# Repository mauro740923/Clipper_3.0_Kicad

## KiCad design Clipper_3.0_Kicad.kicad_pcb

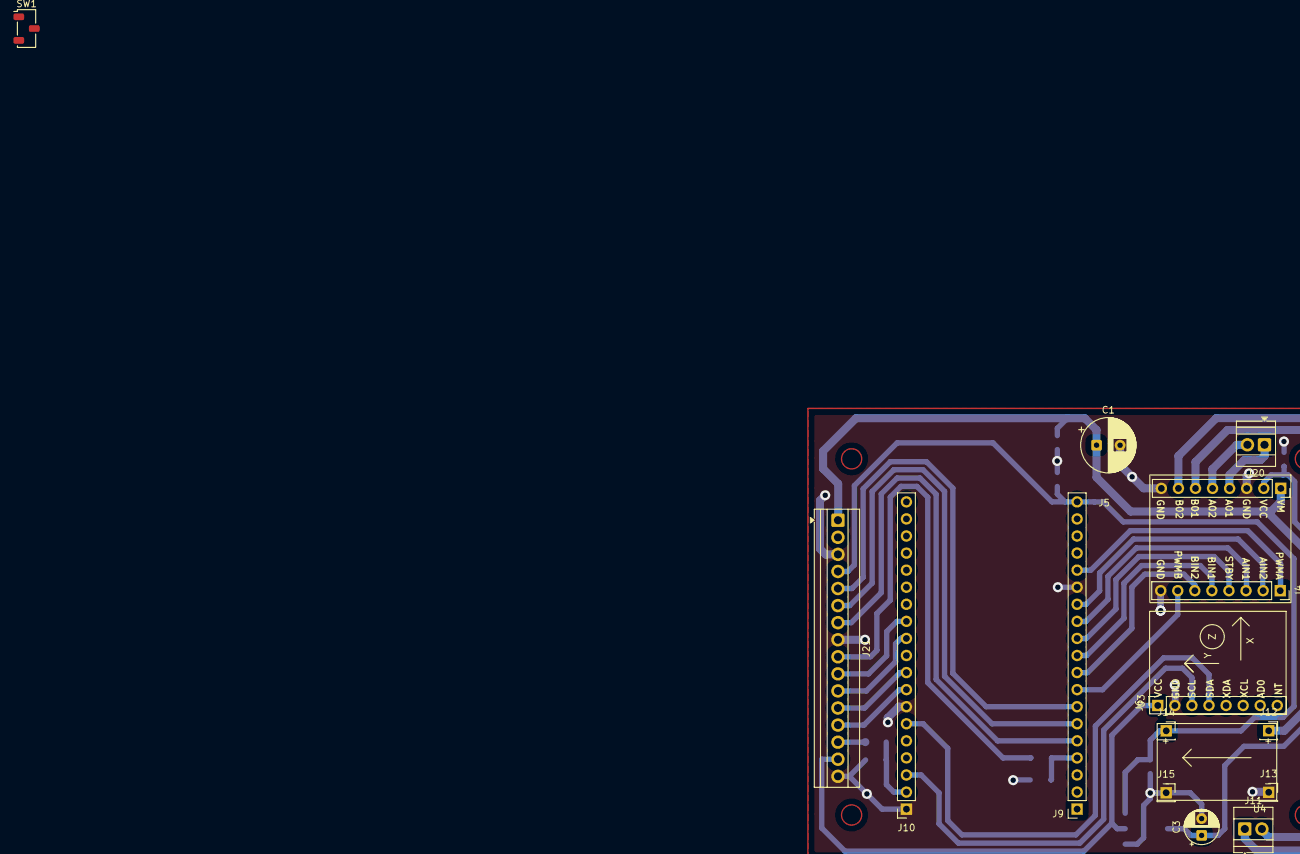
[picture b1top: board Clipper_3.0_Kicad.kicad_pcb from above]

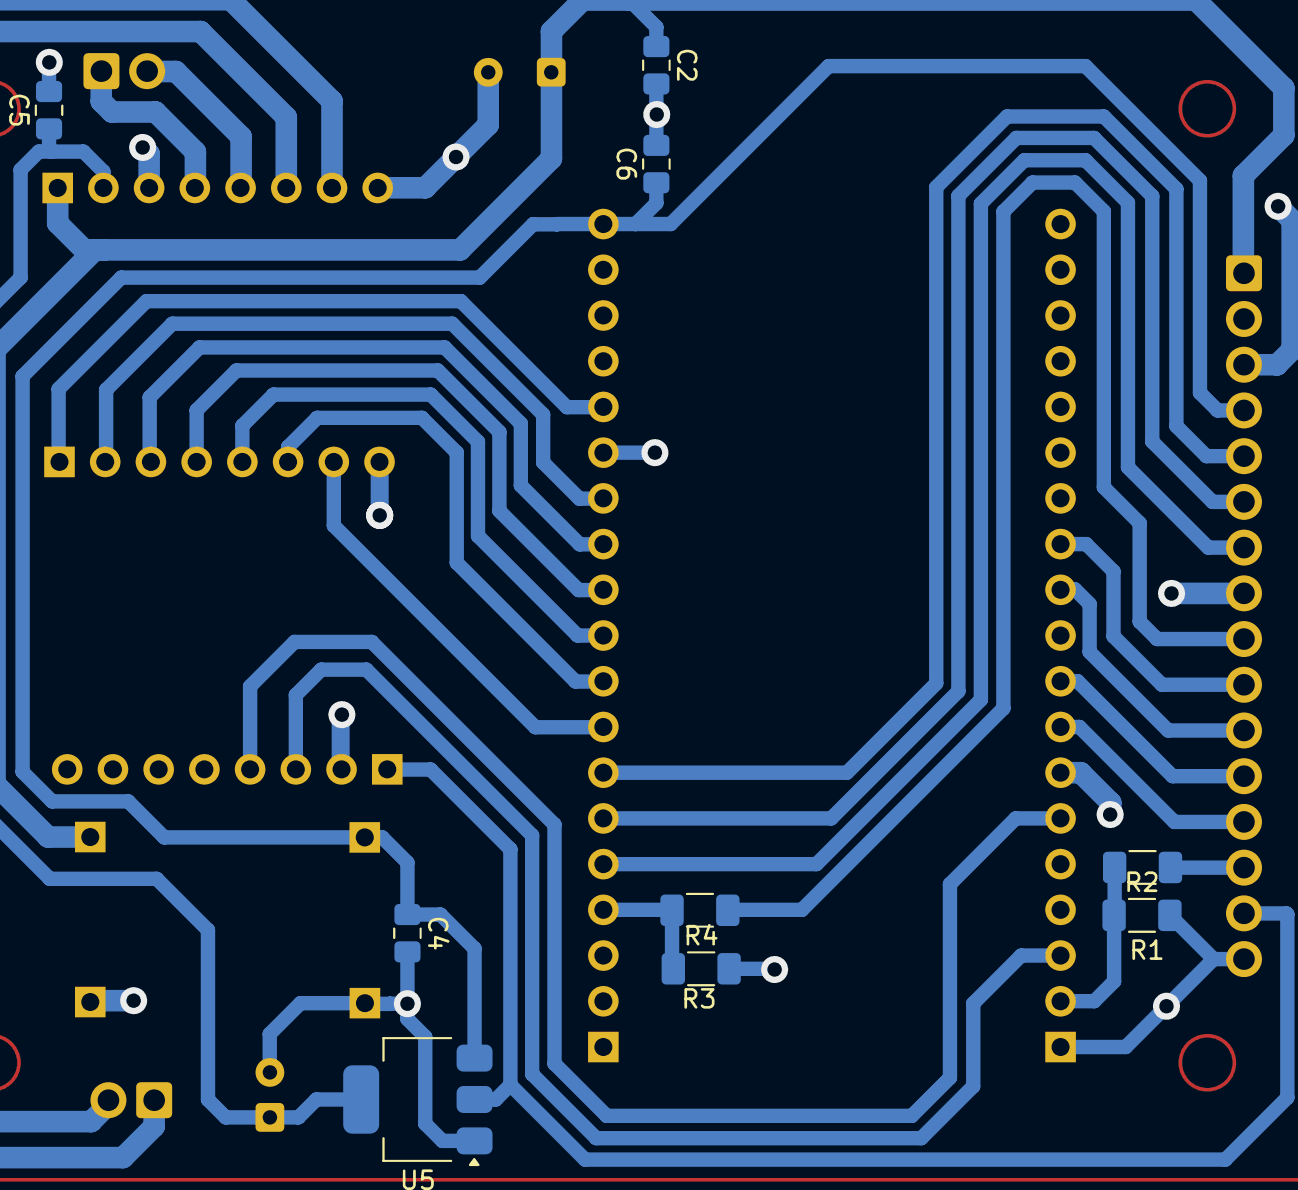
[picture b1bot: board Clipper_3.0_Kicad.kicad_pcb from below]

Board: 2 copper layers, 27 parts (9 on the bottom side), 26 nets.

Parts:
C1: 470uF; CP_Radial_D8.0mm_P3.50mm
C2, C4, C5, C6: 0.1uF; C_0805_2012Metric_Pad1.18x1.45mm_HandSolder
C3: 22uF; CP_Radial_D5.0mm_P2.50mm
J4, J5, J6: Conn_01x08_Socket; PinSocket_1x08_P2.54mm_Vertical
J9, J10: Conn_01x19_Socket; PinSocket_1x19_P2.54mm_Vertical
J11, J20: Screw_Terminal_01x02; TerminalBlock_Xinya_XY308-2.54-2P_1x02_P2.54mm_Horizontal
J12, J13, J14, J15: Conn_01x01_Socket; PinSocket_1x01_P2.54mm_Vertical
J21: Screw_Terminal_01x16; TerminalBlock_Xinya_XY308-2.54-16P_1x16_P2.54mm_Horizontal
R1, R3: 3.3K; R_1206_3216Metric_Pad1.30x1.75mm_HandSolder
R2, R4: 4.7K; R_1206_3216Metric_Pad1.30x1.75mm_HandSolder
SW1: SW_Nidec_CAS-120A1; Nidec_Copal_CAS-120A
U2: TB6612FNG_MODULE; TB6612FNG
U3: GY-521 MODULE; MPU6050_Module
U4: DC/DC Mini360; Mini360_Module
U5: AMS1117-3.3; SOT-223-3_TabPin2

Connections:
/AIN1: J4.14 (Pin_3), J9.12
/AIN2: J4.15 (Pin_2), J9.13
/AO1: J5.4, J20.1
/AO2: J5.5, J20.2
/BIN1: J4.12 (Pin_5), J9.10
/BIN2: J4.11 (Pin_6), J9.9
/BO1: J5.6, J11.2
/BO2: J5.7, J11.1
/PWMA: J4.16 (Pin_1), J9.15
/PWMB: J4.10 (Pin_7), J9.8
/SCL: J6.3, J10.3
/SDA: J6.4, J10.6
/STBY: J4.13 (Pin_4), J9.11
BTN: J9.6, J21.6
ENCD: J9.4, J21.9, R3.1, R3.2, R4.1
ENCI: J10.2, J21.14, R1.1, R1.2, R2.1
GND: C1.2, C2.2, C3.2, C4.2, C5.2, C6.2, J4.9 (Pin_8), J5.3, J5.8, J6.2, J9.14, J10.1, J10.7, J13.1 (Pin_1_1), J15.1 (Pin_1_1), J21.3, J21.8, J21.16, R2.2, R4.2, U5.1 (GND)
LED: J9.7, J21.5
S0: J10.12, J21.10
S1: J10.11, J21.11
S2: J10.9, J21.12
S3: J10.8, J21.13
SIG: J9.5, J21.7
VCC3.3V: C3.1, C5.1, J5.2, J6.1, J21.15, U5.2 (VO)
VCC5V: C4.1, C6.1, J9.19, J14.1 (Pin_1_1), J21.4, U5.3 (VI)
VCC12V: C1.1, C2.1, J5.1, J12.1 (Pin_1_1), J21.1

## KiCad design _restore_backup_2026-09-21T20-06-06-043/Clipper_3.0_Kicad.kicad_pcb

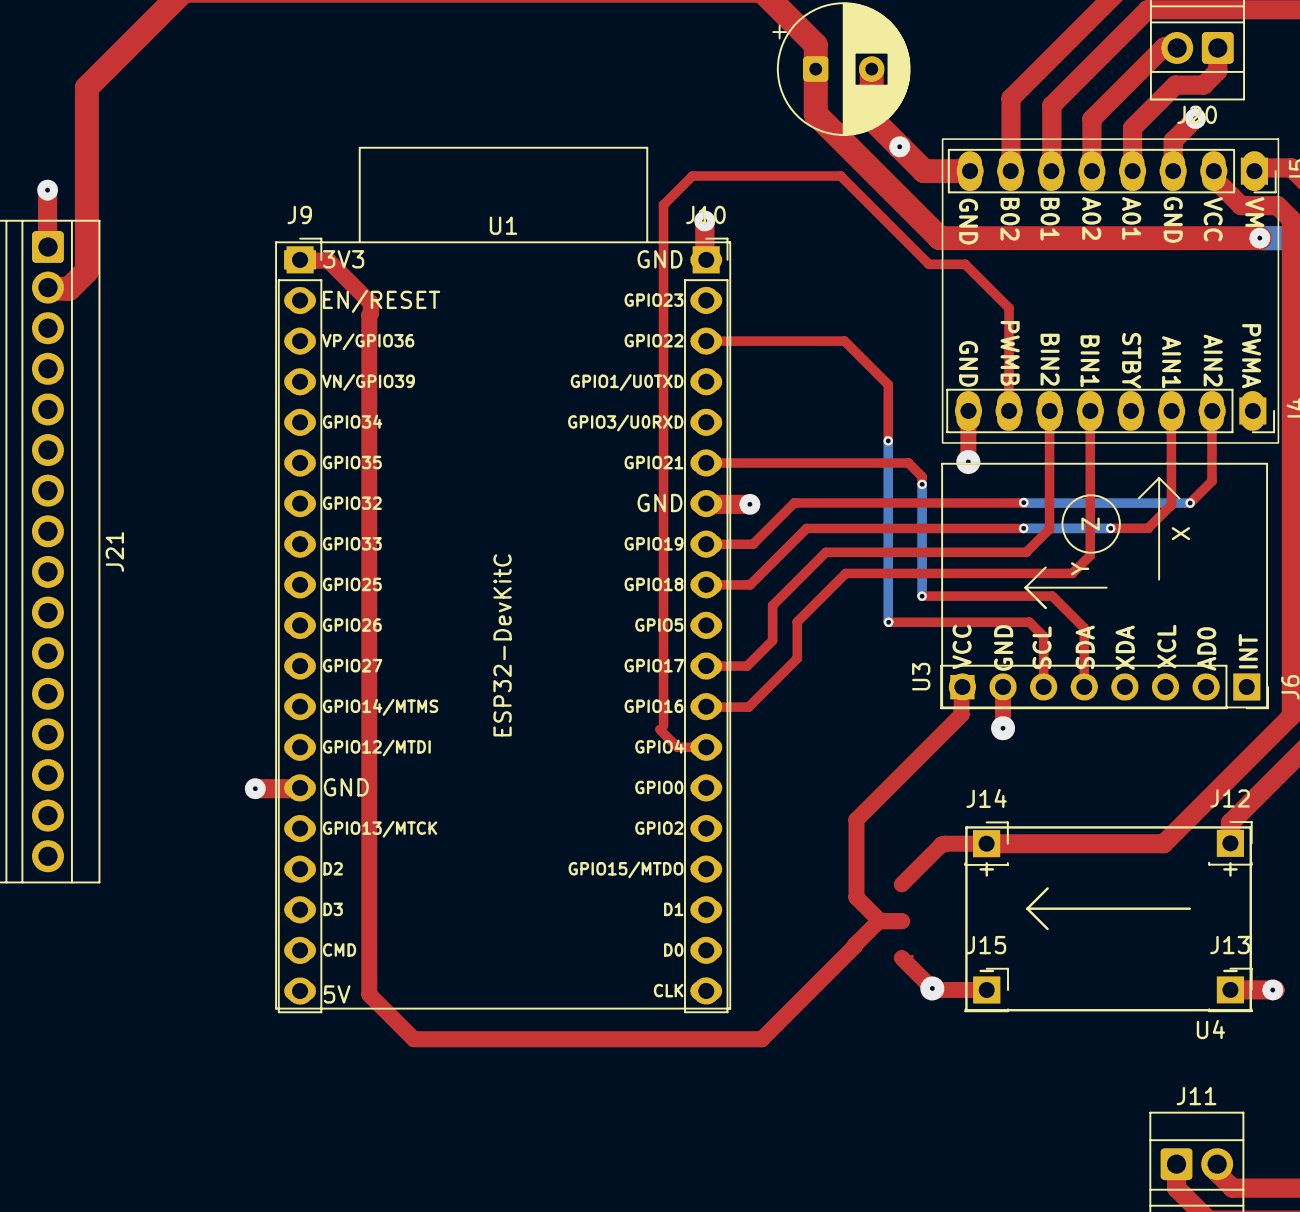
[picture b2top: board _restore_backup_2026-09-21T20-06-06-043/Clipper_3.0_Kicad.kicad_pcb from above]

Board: 2 copper layers, 16 parts (0 on the bottom side), 14 nets.

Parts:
J4, J5, J6: Conn_01x08_Socket; PinSocket_1x08_P2.54mm_Vertical
J9, J10: Conn_01x19_Socket; PinSocket_1x19_P2.54mm_Vertical
J11, J20: Screw_Terminal_01x02; TerminalBlock_Xinya_XY308-2.54-2P_1x02_P2.54mm_Horizontal
J12, J13, J14, J15: Conn_01x01_Socket; PinSocket_1x01_P2.54mm_Vertical
J21: Screw_Terminal_01x16; TerminalBlock_Xinya_XY308-2.54-16P_1x16_P2.54mm_Horizontal
U1: ESP32-DevKitC
U2: TB6612FNG_MODULE; TB6612FNG
U3: GY-521 MODULE; MPU6050_Module
U4: DC/DC MINI-360; Mini360_Module

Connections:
/AIN1: U1.30 (GPIO18), U2.14 (AIN1)
/AIN2: U1.31 (GPIO19), U2.15 (AIN2)
/AO1: J5.4, J20.1
/AO2: J5.5, J20.2
/BIN1: U1.27 (GPIO16), U2.12 (BIN1)
/BIN2: U1.28 (GPIO17), U2.11 (BIN2)
/BO1: J5.6, J11.1
/BO2: J5.7, J11.2
/I2C-CLK: U1.36 (GPIO22), U3.3 (SCL)
/I2C-DATA: U1.33 (GPIO21), U3.4 (SDA)
/PWMA: U1.9 (DAC_1/ADC2_CH8/GPIO25), U2.16 (PWMA)
/PWMB: U1.26 (ADC2_CH0/GPIO4), U2.10 (PWMB)
/STBY: U1.37 (GPIO23), U2.13 (STBY)
GND: J5.3, J5.8, U1.14 (GND), U1.32 (GND), U1.38 (GND)
